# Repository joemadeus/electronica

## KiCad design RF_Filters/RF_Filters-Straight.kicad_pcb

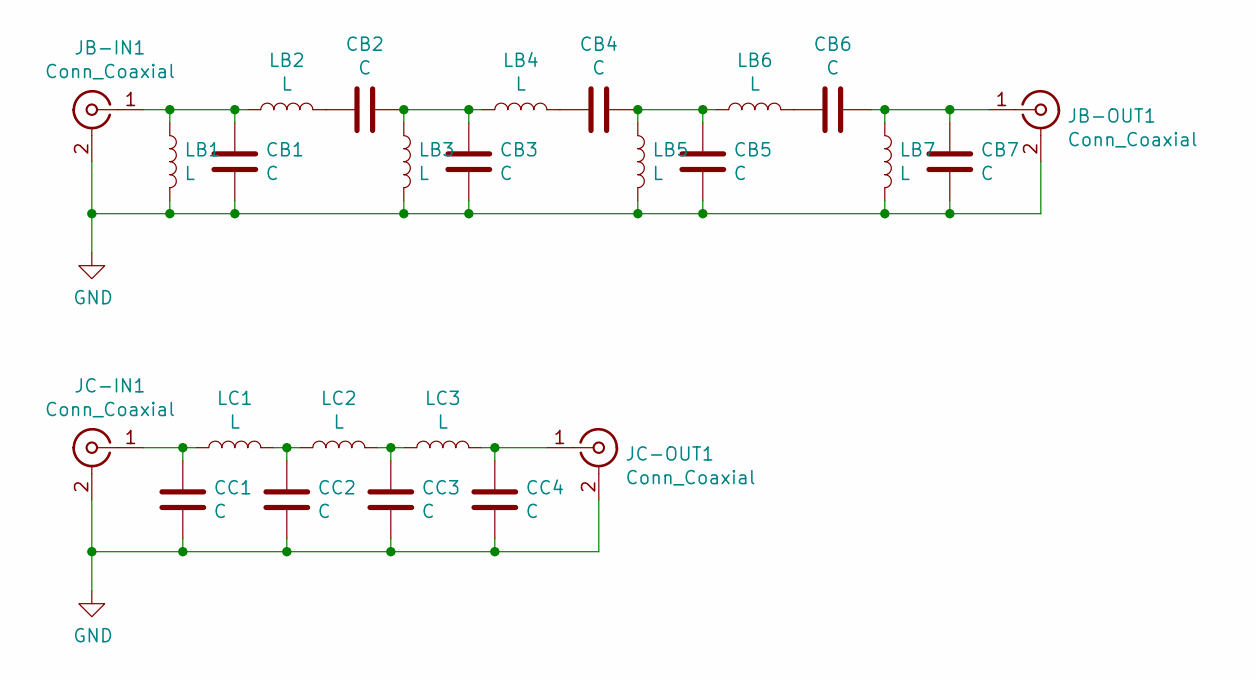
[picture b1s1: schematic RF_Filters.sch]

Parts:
CB1, CB2, CB3, CB4, CB5, CB6, CB7: C; C_0805_2012Metric_Pad1.15x1.40mm_HandSolder
CC1, CC2, CC3, CC4: C; C_0805_2012Metric_Pad1.15x1.40mm_HandSolder
JB-IN1: Conn_Coaxial; SMA_Amphenol_132289_EdgeMount
JB-OUT1: Conn_Coaxial; SMA_Amphenol_132289_EdgeMount
JC-IN1: Conn_Coaxial; SMA_Amphenol_132289_EdgeMount
JC-OUT1: Conn_Coaxial; SMA_Amphenol_132289_EdgeMount
LB1, LB2, LB3, LB4, LB5, LB6, LB7: L; L_0805_2012Metric_Pad1.15x1.40mm_HandSolder
LC1, LC2, LC3: L; L_0805_2012Metric_Pad1.15x1.40mm_HandSolder

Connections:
GND: CB1.2, CB3.2, CB5.2, CB7.2, CC1.2, CC2.2, CC3.2, CC4.2, JB-IN1.2 (Ext), JB-OUT1.2 (Ext), JC-IN1.2 (Ext), JC-OUT1.2 (Ext), LB1.2, LB3.2, LB5.2, LB7.2
unnamed: CB1.1, JB-IN1.1 (In), LB1.1, LB2.1
unnamed: CB2.1, CB3.1, LB3.1, LB4.1
unnamed: CB2.2, LB2.2
unnamed: CB4.1, CB5.1, LB5.1, LB6.1
unnamed: CB4.2, LB4.2
unnamed: CB6.1, CB7.1, JB-OUT1.1 (In), LB7.1
unnamed: CB6.2, LB6.2
unnamed: CC1.1, JC-IN1.1 (In), LC1.1
unnamed: CC2.1, LC1.2, LC2.1
unnamed: CC3.1, LC2.2, LC3.1
unnamed: CC4.1, JC-OUT1.1 (In), LC3.2

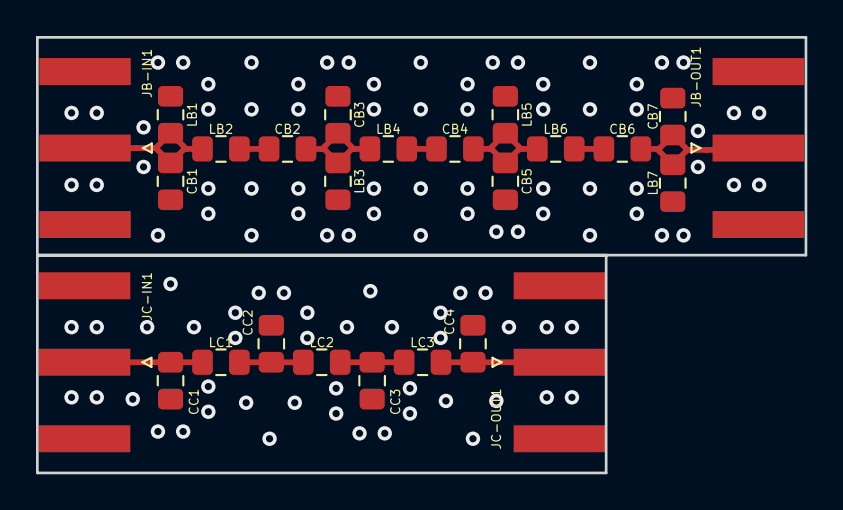
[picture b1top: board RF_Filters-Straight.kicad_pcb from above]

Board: 2 copper layers, 42.7 x 24.2 mm, 25 parts (0 on the bottom side), 12 nets.

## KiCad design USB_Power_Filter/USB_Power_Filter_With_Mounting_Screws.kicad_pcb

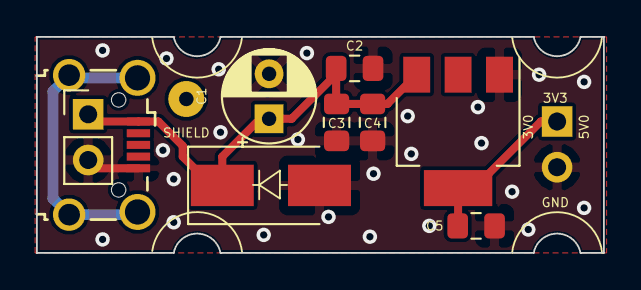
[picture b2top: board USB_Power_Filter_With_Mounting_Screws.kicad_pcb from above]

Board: 2 copper layers, 31.5 x 12.0 mm, 11 parts (1 on the bottom side), 4 nets.

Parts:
C1: 100u; CP_Radial_D5.0mm_P2.50mm
C2: 1uF; C_0805_2012Metric_Pad1.15x1.40mm_HandSolder
C3: 100nF; C_0805_2012Metric_Pad1.15x1.40mm_HandSolder
C4: 1nF; C_0805_2012Metric_Pad1.15x1.40mm_HandSolder
C5: 4.7uF; C_0805_2012Metric_Pad1.15x1.40mm_HandSolder
D1: D_TVS; D_SMB_Handsoldering
POWER1: Conn_01x02_Female; PinHeader_1x02_P2.54mm_Vertical
POWER_IN1: Conn_01x02_Female; PinHeader_1x02_P2.54mm_Vertical
SHIELD: Conn_01x01_Female; SolderWirePad_1x01_Drill0.8mm
U1: LDL1117S; SOT-223-3_TabPin2
USB1: Wuerth_629105150521; USB_Micro-B_Wuerth_629105150521_CircularHoles

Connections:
GND: C1.2, C2.2, C3.2, C4.2, C5.2, D1.2, POWER1.2, POWER_IN1.2, U1.1, USB1.5
unnamed: C1.1, C2.1, C3.1, C4.1, D1.1, POWER_IN1.1, U1.3, USB1.1
unnamed: C5.1, POWER1.1, U1.2
unnamed: SHIELD.1, USB1.6
